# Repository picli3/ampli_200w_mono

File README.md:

# ampli_200w_mono

Amplificador mono de alta potencia, orientado a aplicaciones de audio DIY donde se requiere una sola vía robusta de salida.

## Qué incluye
- esquemáticos o archivos de diseño en KiCad
- PCB o documentación asociada
- base reutilizable para análisis, fabricación o mejora del proyecto

## Propósito general
Este repositorio busca concentrar el diseño de hardware del proyecto en un formato editable y reutilizable, facilitando pruebas, documentación y futuras iteraciones del circuito.

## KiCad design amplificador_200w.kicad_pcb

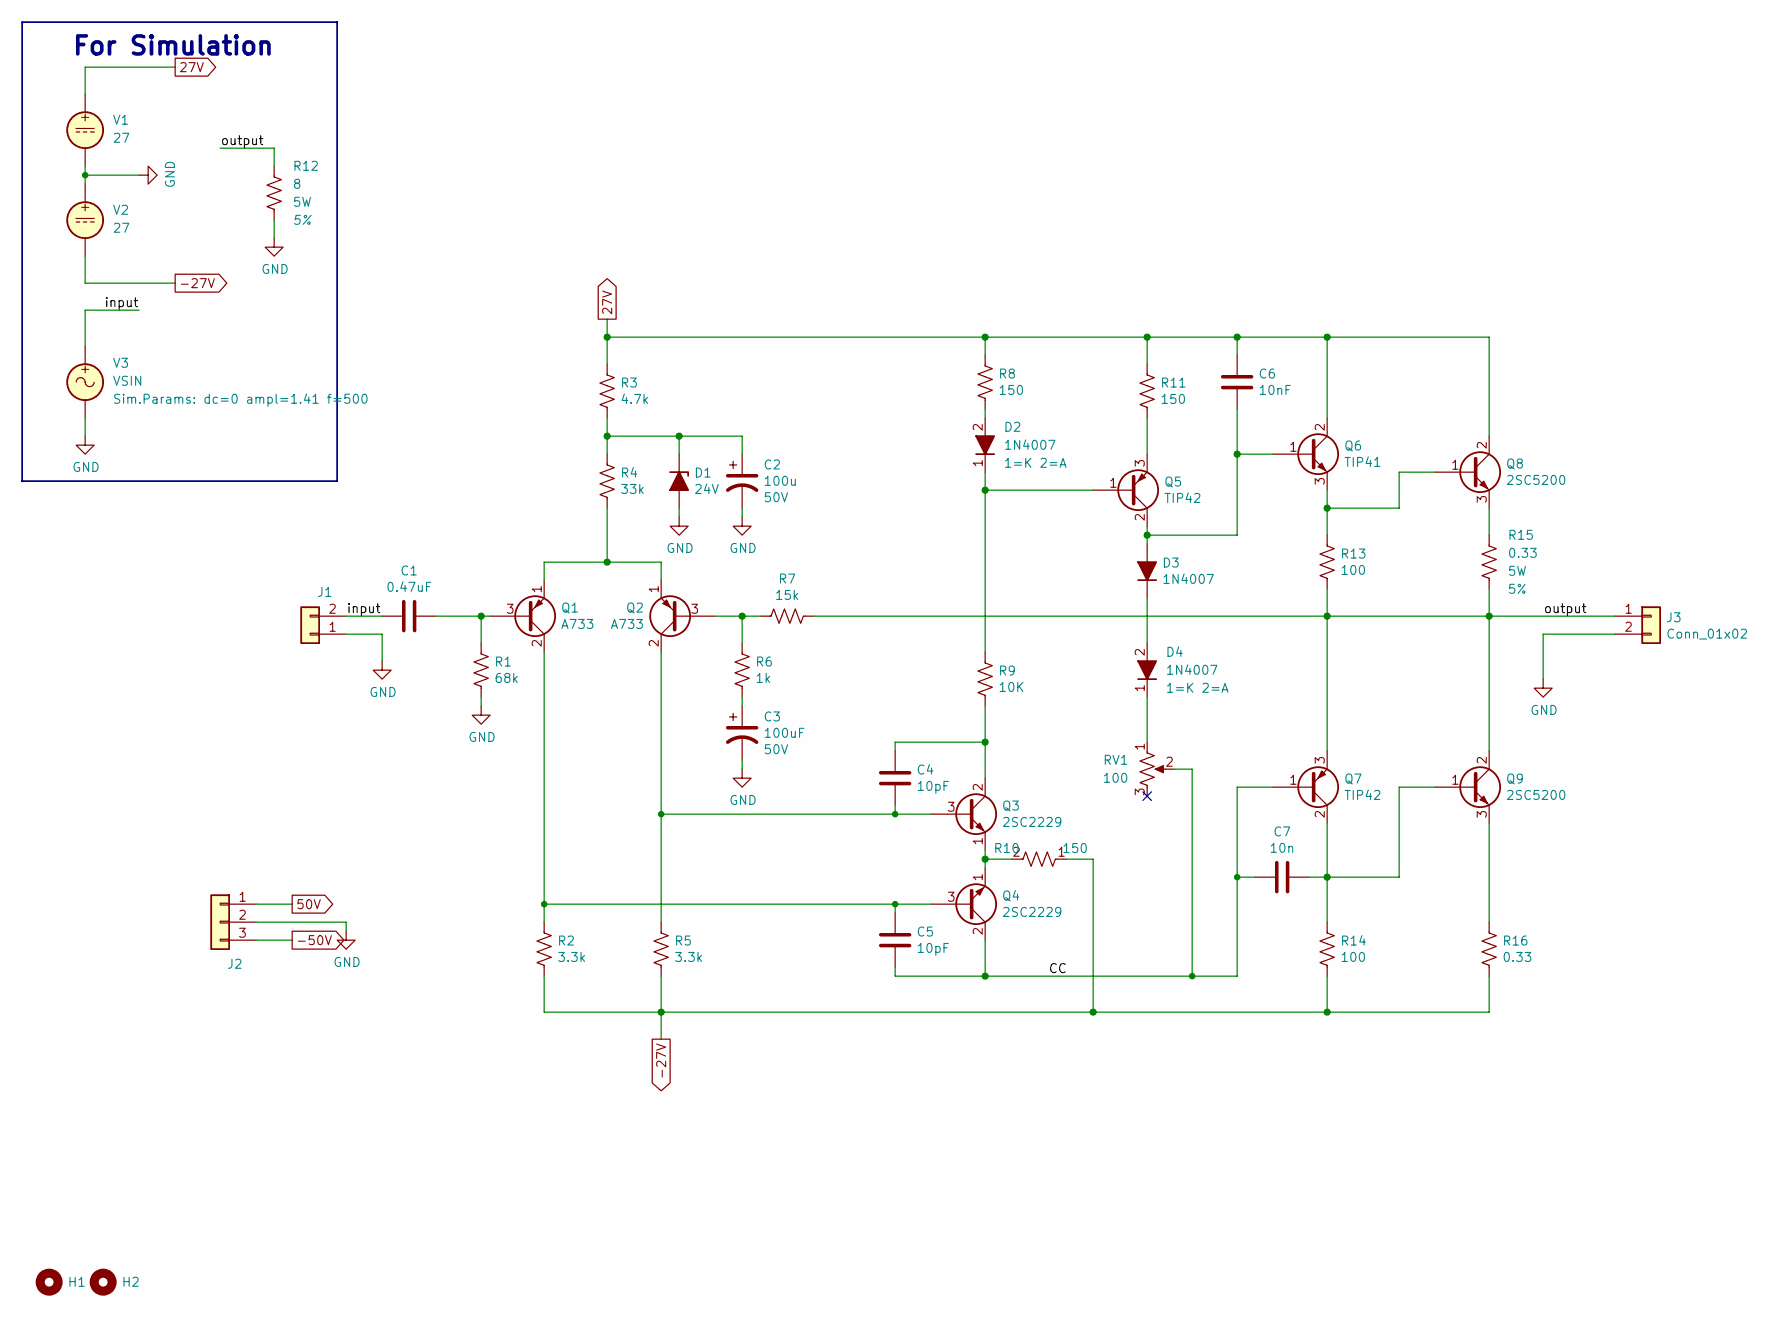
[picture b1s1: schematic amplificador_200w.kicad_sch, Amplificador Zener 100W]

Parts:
C1: 0.47uF; C_Disc_D9.0mm_W2.5mm_P5.00mm
C2: 100u; CP_Radial_D8.0mm_P3.50mm
C3: 100uF; CP_Radial_D8.0mm_P3.50mm
C4, C5: 10pF; C_Disc_D5.0mm_W2.5mm_P5.00mm
C6: 10nF; C_Disc_D9.0mm_W2.5mm_P5.00mm
C7: 10n; C_Disc_D9.0mm_W2.5mm_P5.00mm
D1: 24V; D_A-405_P10.16mm_Horizontal
D2, D3, D4: 1N4007; D_DO-41_SOD81_P10.16mm_Horizontal
H1, H2: MountingHole; MountingHole_3.2mm_M3_Pad_Via
J1: Conn_01x03; PinHeader_1x02_P2.54mm_Vertical
J2: Conn_01x03; TerminalBlock_Phoenix_MKDS-1,5-3-5.08_1x03_P5.08mm_Horizont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
J3: Conn_01x02; TerminalBlock_Phoenix_MKDS-1,5-2-5.08_1x02_P5.08mm_Horizont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
Q1, Q2: A733; TO-92L_HandSolder; Mfg Part # KSA733CGBU
Q3, Q4: 2SC2229; TO-92L_HandSolder
Q5, Q7: TIP42; TO-220-3_Vertical
Q6: TIP41; TO-220-3_Vertical
Q8, Q9: 2SC5200; TO-264-3_Vertical
R1: 68k; R_Axial_DIN0207_L6.3mm_D2.5mm_P7.62mm_Horizontal
R2, R5: 3.3k; R_Axial_DIN0207_L6.3mm_D2.5mm_P7.62mm_Horizontal
R3: 4.7k; R_Axial_DIN0207_L6.3mm_D2.5mm_P7.62mm_Horizontal
R4: 33k; R_Axial_DIN0207_L6.3mm_D2.5mm_P7.62mm_Horizontal
R6: 1k; R_Axial_DIN0207_L6.3mm_D2.5mm_P7.62mm_Horizontal
R7: 15k; R_Axial_DIN0207_L6.3mm_D2.5mm_P7.62mm_Horizontal
R8, R10, R11: 150; R_Axial_DIN0207_L6.3mm_D2.5mm_P7.62mm_Horizontal
R9: 10K; R_Axial_DIN0207_L6.3mm_D2.5mm_P7.62mm_Horizontal
R12: 8; R_Axial_Power_L25.0mm_W9.0mm_P10.16mm_Vertical
R13, R14: 100; R_Axial_DIN0516_L15.5mm_D5.0mm_P20.32mm_Horizontal
R15, R16: 0.33; R_Axial_Power_L25.0mm_W9.0mm_P10.16mm_Vertical
RV1: 100
V1, V2: 27
V3: VSIN

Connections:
-27V: R2.2, R5.2, R10.1, R14.1, R16.1, V2.2
-50V: J2.3
/CC: C5.1, C7.1, Q4.2 (C), Q7.1 (B), RV1.2, RV1.3
/input: C1.2, J1.2, V3.1
/output: J3.1, Q7.3 (E), Q9.2 (C), R7.1, R12.2, R13.1, R15.1
GND: C2.2, C3.2, D1.2 (A), J1.1, J2.2, J3.2, R1.2, R12.1, V1.2, V2.1, V3.2
unnamed: C3.1, R6.2
unnamed: C2.1, D1.1 (K), R3.2, R4.1
unnamed: D2.2 (A), R8.1
unnamed: D2.1 (K), Q5.1 (B), R9.2
unnamed: C6.1, D3.2 (A), Q5.2 (C), Q6.1 (B)
unnamed: D3.1 (K), D4.2 (A)
unnamed: D4.1 (K), RV1.1
unnamed: C1.1, Q1.3 (B), R1.1
unnamed: C5.2, Q1.2 (C), Q4.3 (B), R2.1
unnamed: Q1.1 (E), Q2.1 (E), R4.2
unnamed: Q2.3 (B), R6.1, R7.2
unnamed: C4.1, Q2.2 (C), Q3.3 (B), R5.1
unnamed: C4.2, Q3.2 (C), R9.1
unnamed: Q3.1 (E), Q4.1 (E), R10.2
unnamed: Q5.3 (E), R11.1
unnamed: Q6.3 (E), Q8.1 (B), R13.2
unnamed: C7.2, Q7.2 (C), Q9.1 (B), R14.2
unnamed: Q8.3 (E), R15.2
unnamed: Q9.3 (E), R16.2

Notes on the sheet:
For Simulation

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
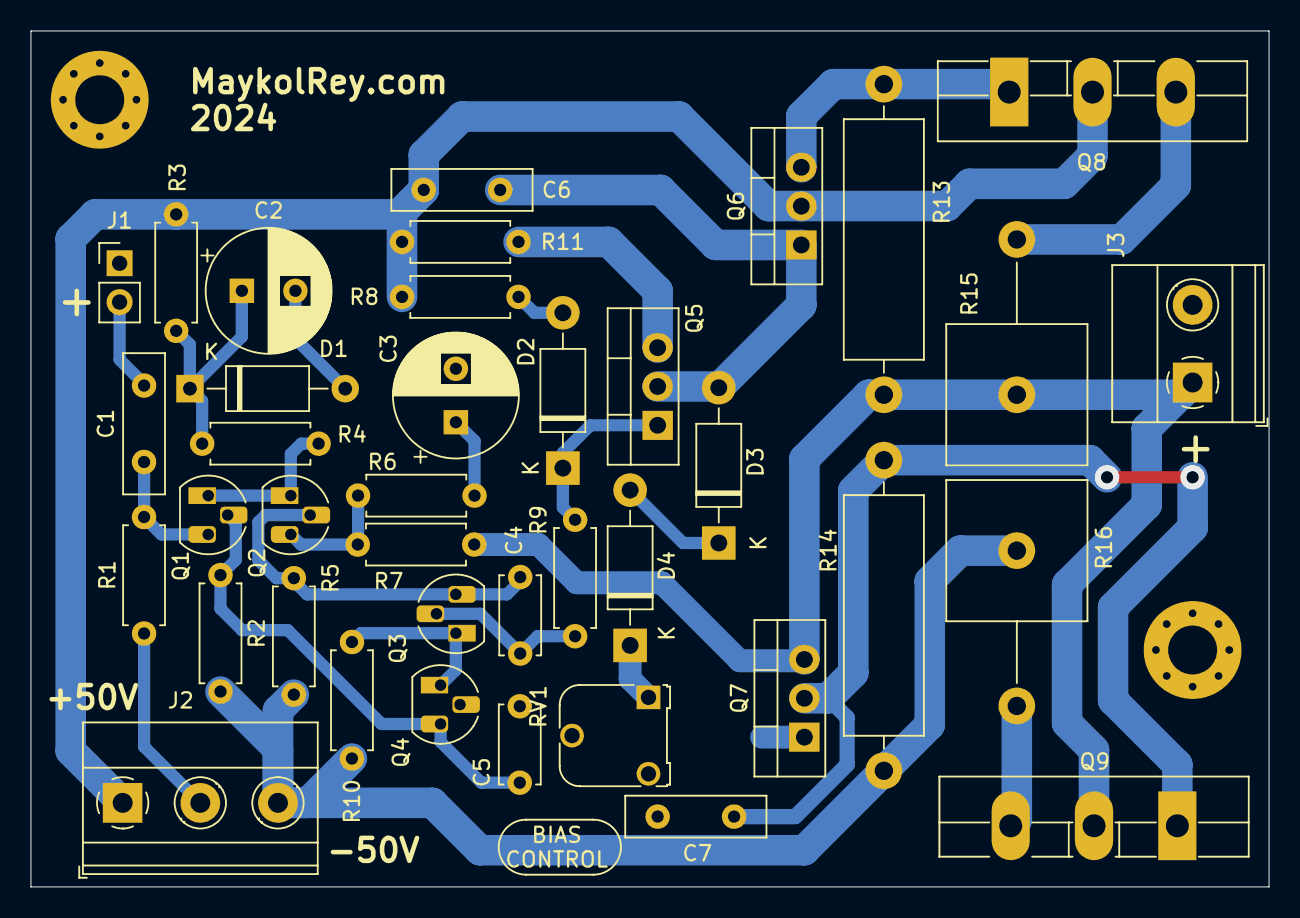
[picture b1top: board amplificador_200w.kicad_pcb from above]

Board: 2 copper layers, 81.0 x 56.0 mm, 41 parts (0 on the bottom side), 25 nets.

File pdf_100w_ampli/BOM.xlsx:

Item | Qty | Reference(s) | Value | LibPart | Footprint | Datasheet | V
1 | 1 | C1 | 0.47uF | Device:C | Capacitor_THT:C_Disc_D9.0mm_W2.5mm_P5.00mm | ~
2 | 2 | C2, C3 | 100uF | Device:CP1 | Capacitor_THT:CP_Radial_D8.0mm_P3.50mm | ~ | 50V
3 | 2 | C4, C5 | 10pF | Device:C | Capacitor_THT:C_Disc_D5.0mm_W2.5mm_P5.00mm | ~
4 | 2 | C6, C7 | 10nF | Device:C | Capacitor_THT:C_Disc_D9.0mm_W2.5mm_P5.00mm | ~
5 | 1 | D1 | 24V | Device:D_Zener_ALT | Diode_THT:D_A-405_P10.16mm_Horizontal | ~
6 | 3 | D2, D3, D4 | 1N4007 | Device:D_ALT | Diode_THT:D_DO-41_SOD81_P10.16mm_Horizontal | ~
7 | 2 | H1, H2 | MountingHole | Mechanical:MountingHole | MountingHole:MountingHole_3.2mm_M3_Pad_Via | ~
8 | 1 | J1 | Conn_01x03 | Connector_Generic:Conn_01x02 | Connector_PinHeader_2.54mm:PinHeader_1x02_P2.54mm_Vertical | ~
9 | 1 | J2 | Conn_01x03 | Connector_Generic:Conn_01x03 | TerminalBlock_Phoenix:TerminalBlock_Phoenix_MKDS-1,5-3-5.08_1x03_P5.08mm_Horizo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 | ~
10 | 1 | J3 | Conn_01x02 | Connector_Generic:Conn_01x02 | TerminalBlock_Phoenix:TerminalBlock_Phoenix_MKDS-1,5-2-5.08_1x02_P5.08mm_Horizo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 | ~
11 | 2 | Q1, Q2 | A733 | Device:Q_PNP_EBC | Package_TO_SOT_THT:TO-92L_HandSolder | https://www.voti.nl/docs/A733.pdf
12 | 2 | Q3, Q4 | 2SC2229 | Device:Q_NPN_ECB | Package_TO_SOT_THT:TO-92L_HandSolder | ~
13 | 2 | Q5, Q7 | TIP42 | Device:Q_PNP_BCE | Package_TO_SOT_THT:TO-220-3_Vertical | ~
14 | 1 | Q6 | TIP41 | Device:Q_NPN_BCE | Package_TO_SOT_THT:TO-220-3_Vertical | ~
15 | 2 | Q8, Q9 | 2SC5200 | Device:Q_NPN_BCE | Package_TO_SOT_THT:TO-264-3_Vertical | ~
16 | 2 | R1, R7 | 68K | Device:R | Resistor_THT:R_Axial_DIN0207_L6.3mm_D2.5mm_P7.62mm_Horizontal | ~
17 | 2 | R2, R5 | 3.3K | Device:R | Resistor_THT:R_Axial_DIN0207_L6.3mm_D2.5mm_P7.62mm_Horizontal | ~
18 | 1 | R3 | 4.7K | Device:R | Resistor_THT:R_Axial_DIN0207_L6.3mm_D2.5mm_P7.62mm_Horizontal | ~
19 | 1 | R4 | 33K | Device:R | Resistor_THT:R_Axial_DIN0207_L6.3mm_D2.5mm_P7.62mm_Horizontal | ~
20 | 1 | R6 | 1K | Device:R | Resistor_THT:R_Axial_DIN0207_L6.3mm_D2.5mm_P7.62mm_Horizontal | ~
21 | 3 | R8, R10, R11 | 150 | Device:R | Resistor_THT:R_Axial_DIN0207_L6.3mm_D2.5mm_P7.62mm_Horizontal | ~
22 | 1 | R9 | 10K | Device:R | Resistor_THT:R_Axial_DIN0207_L6.3mm_D2.5mm_P7.62mm_Horizontal | ~
23 | 2 | R13, R14 | 100 | Device:R | Resistor_THT:R_Axial_DIN0516_L15.5mm_D5.0mm_P20.32mm_Horizontal | ~
24 | 2 | R15, R16 | 0.33 | Device:R | Resistor_THT:R_Axial_Power_L25.0mm_W9.0mm_P10.16mm_Vertical | ~
25 | 1 | RV1 | 1K | Device:R_POT | Potentiometer_THT:Potentiometer_Runtron_RM-065_Vertical | ~

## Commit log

2021-12-11 version provada
2024-06-27 enviando a fabricar a jlcpcb
2024-08-07 version simulada y probada en la realidad
2026-04-29 Agrega README con descripción inicial del proyecto
